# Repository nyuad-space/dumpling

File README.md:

## Hardware Errata v1 (2025)

- Pull down Boot1 instead of floating. For booting F405 with DFU, hold down the 3rd reset button.
- SWD TagConnect: Layout is too close to XT30 or M.2 sockets and connector is difficult to source.
- DRC check (recheck unconnected items).
- Look out for "x"ed POS in the BOM file. May have been accidentally toggled off.
- Reset button is too small & hard to reach
- Vertical USB is less stress-tolerant (pulls on solder)
- STM32F411 DFU bootloading error
- Check forward current rating for Schottky diodes.
- Consider using more current sensors i.e. Measure current draw from each board, from VIN total etc.
- Add in extra LEDs, buttons, etc. for extra functions/debugging in the future
- Unless saving space is a priority, consider using 0603 instead of 0402 for easier potential fixes
- Misc. Consider a more impact-tolerant casing to protect board upon landing

# Data Dumpling

Data Dumpling is a modular, high-speed data logger for MEMS sensors, designed as a payload for our experimental sounding rocket Stage Fright (2025). It enables real-time characterization and benchmarking of commercial sensors in demanding flight environments. The project aims to support sensor research and promote scalable, plug-and-play architectures for future space missions.

---

## Features

- **Modular Architecture**: Hot-swappable M.2 sensor ports with dedicated coprocessors  
- **Sensor Compatibility**: Supports I2C/SPI sensors with auto-detection via WHO_AM_I or equivalent registers  
- **Dedicated Flash Memory**: Each sensor board logs to onboard 16MB non-volatile memory  
- **Universal Firmware**: One firmware for all sensor types—detects, initializes, logs, and stores automatically  
- **Flight-Triggered Logging**: Dual-buffered flash logging triggered by flight detection events  
- **Core MCU**: STM32F405 manages flight readiness and triggers; STM32F411 handles individual sensor boards  
- **Post-Flight Retrieval**: Optionally offloads sensor data to SD card after recovery  

---

## Applications

- Benchmarking MEMS sensors in realistic aerospace environments  
- Development of sensor fusion algorithms and accurate sensor models  
- Modular data collection for experimental payloads  
- Plug-and-play architecture for custom flight computers and high-speed telemetry systems  

---

## Mainboard Components

| Type        | Components                                    |
|-------------|-----------------------------------------------|
| Main MCU    | STM32F405RGT                                  |
| Coprocessor | STM32F411CEU6                                 |
| IMUs        | LSM6DSO32, BMI088                              |
| Barometers  | DPS310XTSA1, BMP390L                           |
| Magnetometer| LIS2MDLTR                                      |
| Temperature | HDC3022DEJR                                    |
| Flash       | 16MB SPI NOR Flash per sensor board           |
| Recovery    | SD card slot for post-flight data offload     |

---

## Firmware Overview

Each STM32 microcontroller is programmed via built-in USB DFU bootloader.

### Main processor
- Communicates with MPU6050 to determine upright position
- Triggers flight monitoring upon launch detection
- Manages three flash files:
  - **Circular Buffer**: Logs during flight-ready state with overwrite on overflow  
  - **Main Buffer**: Logs during flight, no wrap-around  
  - **Status File**: Logs sensor configuration, buffer states, memory info, etc.  

### Coprocessor
Each sensor board follows this universal sequence:

1. Detect sensor using WHO_AM_I (or equivalent)  
2. Initialize I2C or SPI communication  
3. Configure sensor parameters (range, ODR, oversampling, filters)  
4. Initialize filesystem and create sensor-specific files  
5. Log sensor data at configured rate to flash memory  

---

## Future Improvements

- Integrate RTOS for multitasking, task prioritization, and modular firmware structure
- Add wireless/CAN telemetry  
- Increase flash capacity and add compression  
- Expand to include GNSS, radiation, and vibration sensors  
- Enable real-time in-flight filtering and basic analytics
- Use UART for master-slave communication in Arduino framework (SPI doesn't support it by default)
- Ensure unique flash IDs and file headers per sensor for proper data parsing

---

## Notes

- Designed for SRAD rocketry — ensure proper mechanical and EMI shielding  
- Verify sensor electrical compatibility before connecting new boards  
- Maintain synchronized firmware versions across all sensor modules  
- Follow proper ESD precautions during handling and flashing  

---

## Disclaimer

Use the files, hardware, and software in this repository at your own risk.  
We assume no liability for hardware damage, software malfunction, or unexpected behavior, particularly during live flight testing.  
Always validate your configuration through extensive ground testing.

---

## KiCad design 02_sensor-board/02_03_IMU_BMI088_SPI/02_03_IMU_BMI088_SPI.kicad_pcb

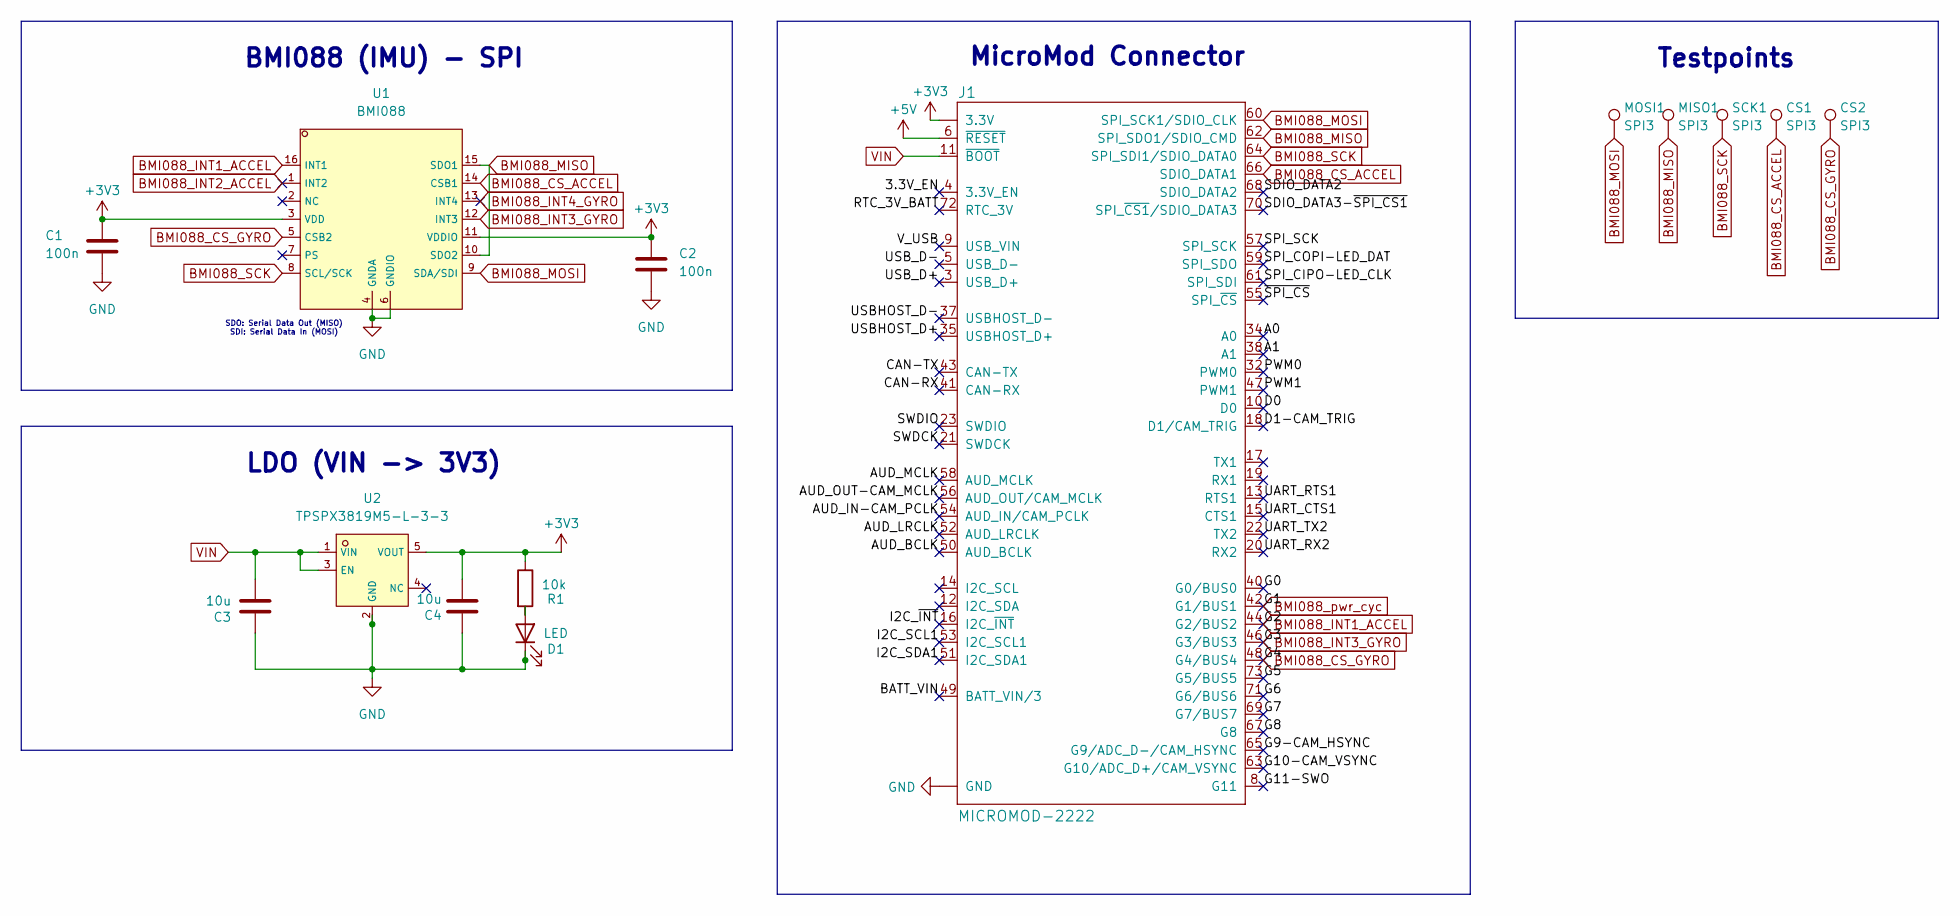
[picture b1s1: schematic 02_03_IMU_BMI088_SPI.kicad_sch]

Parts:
C1, C2: 100n; C_0402_1005Metric
C3, C4: 10u; C_1206_3216Metric
CS1, CS2: SPI3; TestPoint_Pad_D1.0mm
D1: LED; LED_0603_1608Metric
J1: MICROMOD-2222; M.2-CARD-E-22
MISO1: SPI3; TestPoint_Pad_D1.0mm
MOSI1: SPI3; TestPoint_Pad_D1.0mm
R1: 10k; R_0603_1608Metric
SCK1: SPI3; TestPoint_Pad_D1.0mm
U1: BMI088; LGA-16_L4.5-W3.0-P0.50-BL; LCSC C194919
U2: TPSPX3819M5-L-3-3; SOT-23-5_L3.0-W1.6-P0.95-LS2.8-BR; LCSC C5370980

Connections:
+3V3: C1.1, C2.1, C4.1, J1.2 (3.3V), J1.74 (3.3V), R1.1, U1.3 (VDD), U1.11 (VDDIO), U2.5 (VOUT)
+5V: J1.6 (~RESET)
/3.3V_EN: J1.4 (3.3V_EN)
/A0: J1.34 (A0)
/A1: J1.38 (A1)
/AUD_BCLK: J1.50 (AUD_BCLK)
/AUD_IN-CAM_PCLK: J1.54 (AUD_IN/CAM_PCLK)
/AUD_LRCLK: J1.52 (AUD_LRCLK)
/AUD_MCLK: J1.58 (AUD_MCLK)
/AUD_OUT-CAM_MCLK: J1.56 (AUD_OUT/CAM_MCLK)
/BATT_VIN: J1.49 (BATT_VIN/3)
/CAN-RX: J1.41 (CAN-RX)
/CAN-TX: J1.43 (CAN-TX)
/D0: J1.10 (D0)
/D1-CAM_TRIG: J1.18 (D1/CAM_TRIG)
/G0: J1.40 (G0/BUS0)
/G5: J1.73 (G5/BUS5)
/G6: J1.71 (G6/BUS6)
/G7: J1.69 (G7/BUS7)
/G8: J1.67 (G8)
/G9-CAM_HSYNC: J1.65 (G9/ADC_D-/CAM_HSYNC)
/G10-CAM_VSYNC: J1.63 (G10/ADC_D+/CAM_VSYNC)
/G11-SWO: J1.8 (G11)
/I2C_SCL1: J1.53 (I2C_SCL1)
/I2C_SDA1: J1.51 (I2C_SDA1)
/I2C_~INT: J1.16 (I2C_~INT)
/PWM0: J1.32 (PWM0)
/PWM1: J1.47 (PWM1)
/RTC_3V_BATT: J1.72 (RTC_3V)
/SDIO_DATA2: J1.68 (SDIO_DATA2)
/SDIO_DATA3-~SPI_CS1: J1.70 (SPI_~CS1/SDIO_DATA3)
/SPI_CIPO-LED_CLK: J1.61 (SPI_SDI)
/SPI_COPI-LED_DAT: J1.59 (SPI_SDO)
/SPI_SCK: J1.57 (SPI_SCK)
/SWDCK: J1.21 (SWDCK)
/SWDIO: J1.23 (SWDIO)
/UART_CTS1: J1.15 (CTS1)
/UART_RTS1: J1.13 (RTS1)
/UART_RX2: J1.20 (RX2)
/UART_TX2: J1.22 (TX2)
/USBHOST_D+: J1.35 (USBHOST_D+)
/USBHOST_D-: J1.37 (USBHOST_D-)
/USB_D+: J1.3 (USB_D+)
/USB_D-: J1.5 (USB_D-)
/V_USB: J1.9 (USB_VIN)
/~SPI_CS: J1.55 (SPI_~CS)
BMI088_CS_ACCEL: CS1.1, J1.66 (SDIO_DATA1), U1.14 (CSB1)
BMI088_CS_GYRO: CS2.1, J1.48 (G4/BUS4), U1.5 (CSB2)
BMI088_INT1_ACCEL: J1.44 (G2/BUS2), U1.16 (INT1)
BMI088_INT2_ACCEL: U1.1 (INT2)
BMI088_INT3_GYRO: J1.46 (G3/BUS3), U1.12 (INT3)
BMI088_INT4_GYRO: U1.13 (INT4)
BMI088_MISO: J1.62 (SPI_SDO1/SDIO_CMD), MISO1.1, U1.10 (SDO2), U1.15 (SDO1)
BMI088_MOSI: J1.60 (SPI_SCK1/SDIO_CLK), MOSI1.1, U1.9 (SDA/SDI)
BMI088_SCK: J1.64 (SPI_SDI1/SDIO_DATA0), SCK1.1, U1.8 (SCL/SCK)
BMI088_pwr_cyc: J1.42 (G1/BUS1)
GND: C1.2, C2.2, C3.2, C4.2, D1.1 (K), J1.1 (GND), J1.7 (GND), J1.33 (GND), J1.36 (GND), J1.39 (GND), J1.45 (GND), J1.75 (GND), J1.GND1 (GND), J1.GND2 (GND), J1.GND3 (GND), U1.4 (GNDA), U1.6 (GNDIO), U2.2 (GND)
unnamed: D1.2 (A), R1.2
VIN: C3.1, J1.11 (~BOOT), U2.1 (VIN), U2.3 (EN)

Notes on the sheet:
Testpoints
BMI088 (IMU) - SPI
SDO: Serial Data Out (MISO) SDI: Serial Data In (MOSI)
MicroMod Connector
LDO (VIN -> 3V3)

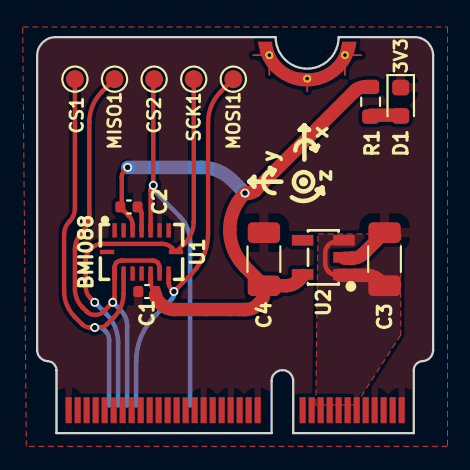
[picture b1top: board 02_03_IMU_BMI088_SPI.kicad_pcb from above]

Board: 2 copper layers, 22.0 x 22.0 mm, 16 parts (0 on the bottom side), 11 nets.

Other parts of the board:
FRAME1: FRAME-LEDGER; CREATIVE_COMMONS
LOGO1: SPECIAL_INSTRUCTIONS-ORDERING; ORDERING_INSTRUCTIONS

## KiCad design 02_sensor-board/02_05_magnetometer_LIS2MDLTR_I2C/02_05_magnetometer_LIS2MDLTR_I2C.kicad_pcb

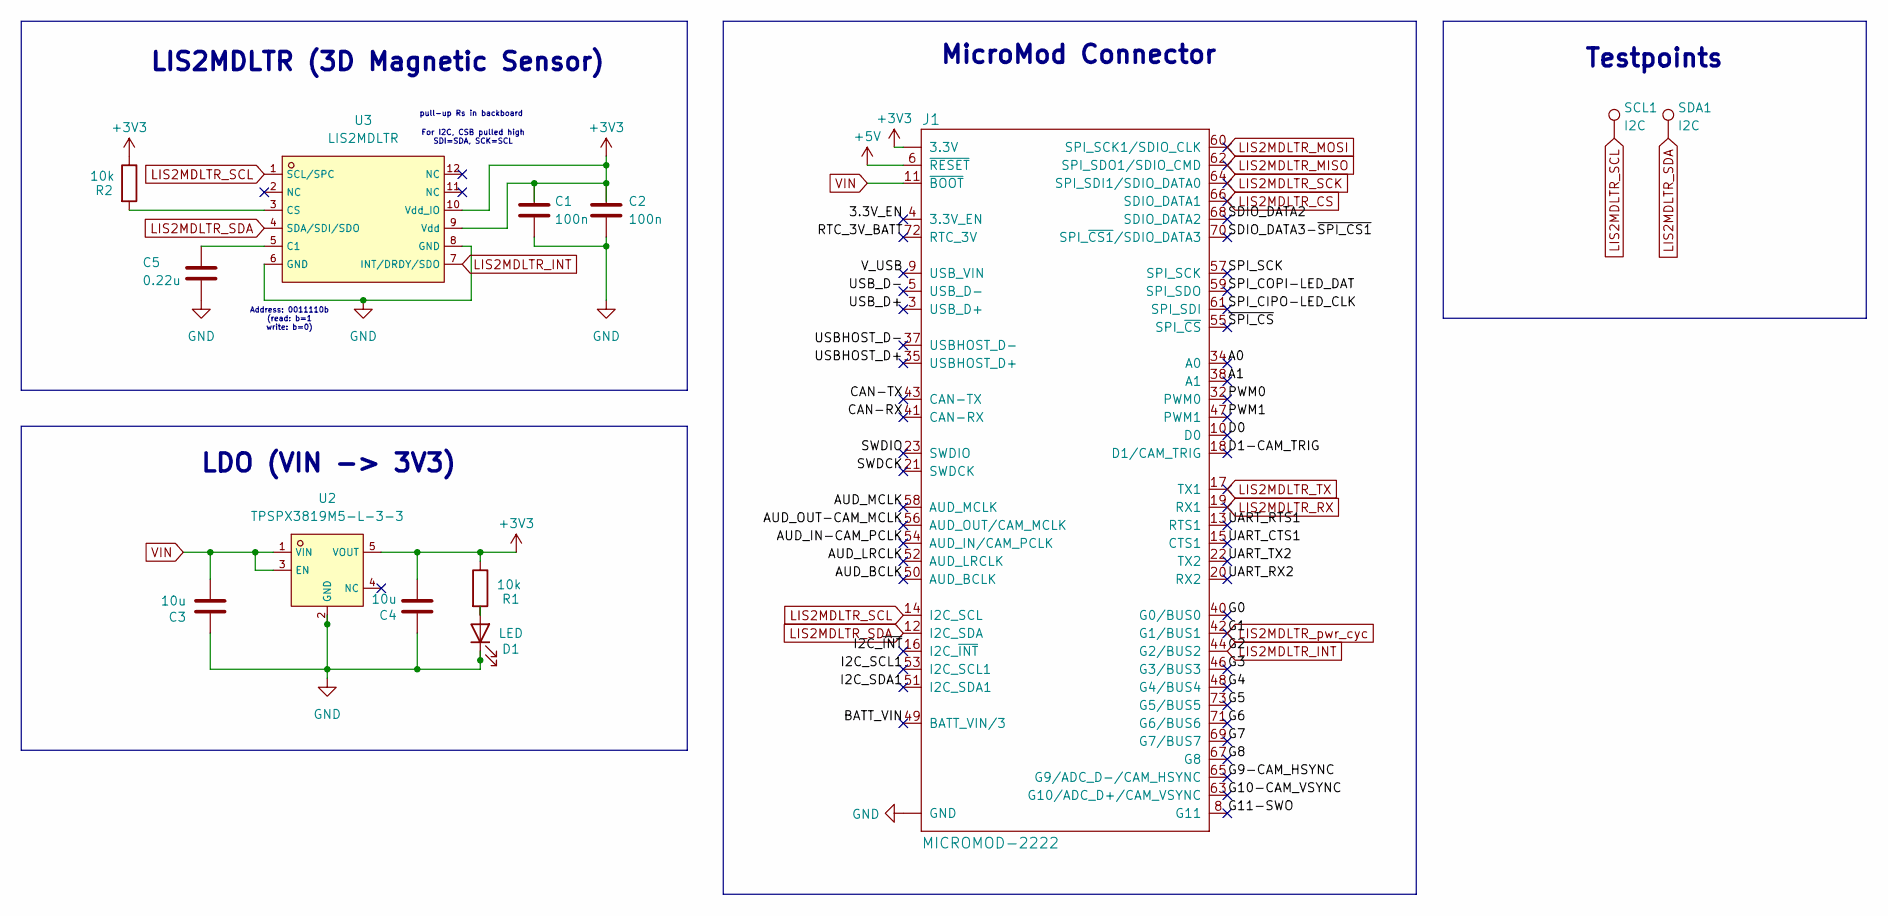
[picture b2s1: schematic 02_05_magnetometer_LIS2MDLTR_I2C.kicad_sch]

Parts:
C1, C2: 100n; C_0402_1005Metric
C3, C4: 10u; C_1206_3216Metric
C5: 0.22u; C_0402_1005Metric
D1: LED; LED_0603_1608Metric
J1: MICROMOD-2222; M.2-CARD-E-22
R1: 10k; R_0603_1608Metric
R2: 10k; R_0402_1005Metric
SCL1: I2C; TestPoint_Pad_D1.0mm
SDA1: I2C; TestPoint_Pad_D1.0mm
U2: TPSPX3819M5-L-3-3; SOT-23-5_L3.0-W1.6-P0.95-LS2.8-BR; LCSC C5370980
U3: LIS2MDLTR; LGA-12_L2.0-W2.0-P0.50-BL; LCSC C919695

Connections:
+3V3: C1.1, C2.1, C4.1, J1.2 (3.3V), J1.74 (3.3V), R1.1, R2.1, U2.5 (VOUT), U3.9 (Vdd), U3.10 (Vdd_IO)
+5V: J1.6 (~RESET)
/3.3V_EN: J1.4 (3.3V_EN)
/A0: J1.34 (A0)
/A1: J1.38 (A1)
/AUD_BCLK: J1.50 (AUD_BCLK)
/AUD_IN-CAM_PCLK: J1.54 (AUD_IN/CAM_PCLK)
/AUD_LRCLK: J1.52 (AUD_LRCLK)
/AUD_MCLK: J1.58 (AUD_MCLK)
/AUD_OUT-CAM_MCLK: J1.56 (AUD_OUT/CAM_MCLK)
/BATT_VIN: J1.49 (BATT_VIN/3)
/CAN-RX: J1.41 (CAN-RX)
/CAN-TX: J1.43 (CAN-TX)
/D0: J1.10 (D0)
/D1-CAM_TRIG: J1.18 (D1/CAM_TRIG)
/G0: J1.40 (G0/BUS0)
/G3: J1.46 (G3/BUS3)
/G4: J1.48 (G4/BUS4)
/G5: J1.73 (G5/BUS5)
/G6: J1.71 (G6/BUS6)
/G7: J1.69 (G7/BUS7)
/G8: J1.67 (G8)
/G9-CAM_HSYNC: J1.65 (G9/ADC_D-/CAM_HSYNC)
/G10-CAM_VSYNC: J1.63 (G10/ADC_D+/CAM_VSYNC)
/G11-SWO: J1.8 (G11)
/I2C_SCL1: J1.53 (I2C_SCL1)
/I2C_SDA1: J1.51 (I2C_SDA1)
/I2C_~INT: J1.16 (I2C_~INT)
/PWM0: J1.32 (PWM0)
/PWM1: J1.47 (PWM1)
/RTC_3V_BATT: J1.72 (RTC_3V)
/SDIO_DATA2: J1.68 (SDIO_DATA2)
/SDIO_DATA3-~SPI_CS1: J1.70 (SPI_~CS1/SDIO_DATA3)
/SPI_CIPO-LED_CLK: J1.61 (SPI_SDI)
/SPI_COPI-LED_DAT: J1.59 (SPI_SDO)
/SPI_SCK: J1.57 (SPI_SCK)
/SWDCK: J1.21 (SWDCK)
/SWDIO: J1.23 (SWDIO)
/UART_CTS1: J1.15 (CTS1)
/UART_RTS1: J1.13 (RTS1)
/UART_RX2: J1.20 (RX2)
/UART_TX2: J1.22 (TX2)
/USBHOST_D+: J1.35 (USBHOST_D+)
/USBHOST_D-: J1.37 (USBHOST_D-)
/USB_D+: J1.3 (USB_D+)
/USB_D-: J1.5 (USB_D-)
/V_USB: J1.9 (USB_VIN)
/~SPI_CS: J1.55 (SPI_~CS)
GND: C1.2, C2.2, C3.2, C4.2, C5.2, D1.1 (K), J1.1 (GND), J1.7 (GND), J1.33 (GND), J1.36 (GND), J1.39 (GND), J1.45 (GND), J1.75 (GND), J1.GND1 (GND), J1.GND2 (GND), J1.GND3 (GND), U2.2 (GND), U3.6 (GND), U3.8 (GND)
LIS2MDLTR_CS: J1.66 (SDIO_DATA1)
LIS2MDLTR_INT: J1.44 (G2/BUS2), U3.7 (INT/DRDY/SDO)
LIS2MDLTR_MISO: J1.62 (SPI_SDO1/SDIO_CMD)
LIS2MDLTR_MOSI: J1.60 (SPI_SCK1/SDIO_CLK)
LIS2MDLTR_RX: J1.19 (RX1)
LIS2MDLTR_SCK: J1.64 (SPI_SDI1/SDIO_DATA0)
LIS2MDLTR_SCL: J1.14 (I2C_SCL), SCL1.1, U3.1 (SCL/SPC)
LIS2MDLTR_SDA: J1.12 (I2C_SDA), SDA1.1, U3.4 (SDA/SDI/SDO)
LIS2MDLTR_TX: J1.17 (TX1)
LIS2MDLTR_pwr_cyc: J1.42 (G1/BUS1)
unnamed: D1.2 (A), R1.2
unnamed: C5.1, U3.5 (C1)
unnamed: R2.2, U3.3 (CS)
VIN: C3.1, J1.11 (~BOOT), U2.1 (VIN), U2.3 (EN)

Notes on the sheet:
pull-up Rs in backboard
Address: 0011110b (read: b=1 write: b=0)
MicroMod Connector
LDO (VIN -> 3V3)
LIS2MDLTR (3D Magnetic Sensor)
For I2C, CSB pulled high SDI=SDA, SCK=SCL
Testpoints

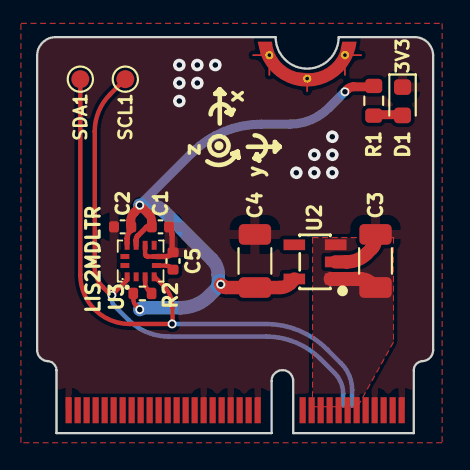
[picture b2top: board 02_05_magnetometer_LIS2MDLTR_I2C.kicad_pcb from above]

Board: 2 copper layers, 22.0 x 22.0 mm, 15 parts (0 on the bottom side), 9 nets.

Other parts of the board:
FRAME1: FRAME-LEDGER; CREATIVE_COMMONS
LOGO1: SPECIAL_INSTRUCTIONS-ORDERING; ORDERING_INSTRUCTIONS

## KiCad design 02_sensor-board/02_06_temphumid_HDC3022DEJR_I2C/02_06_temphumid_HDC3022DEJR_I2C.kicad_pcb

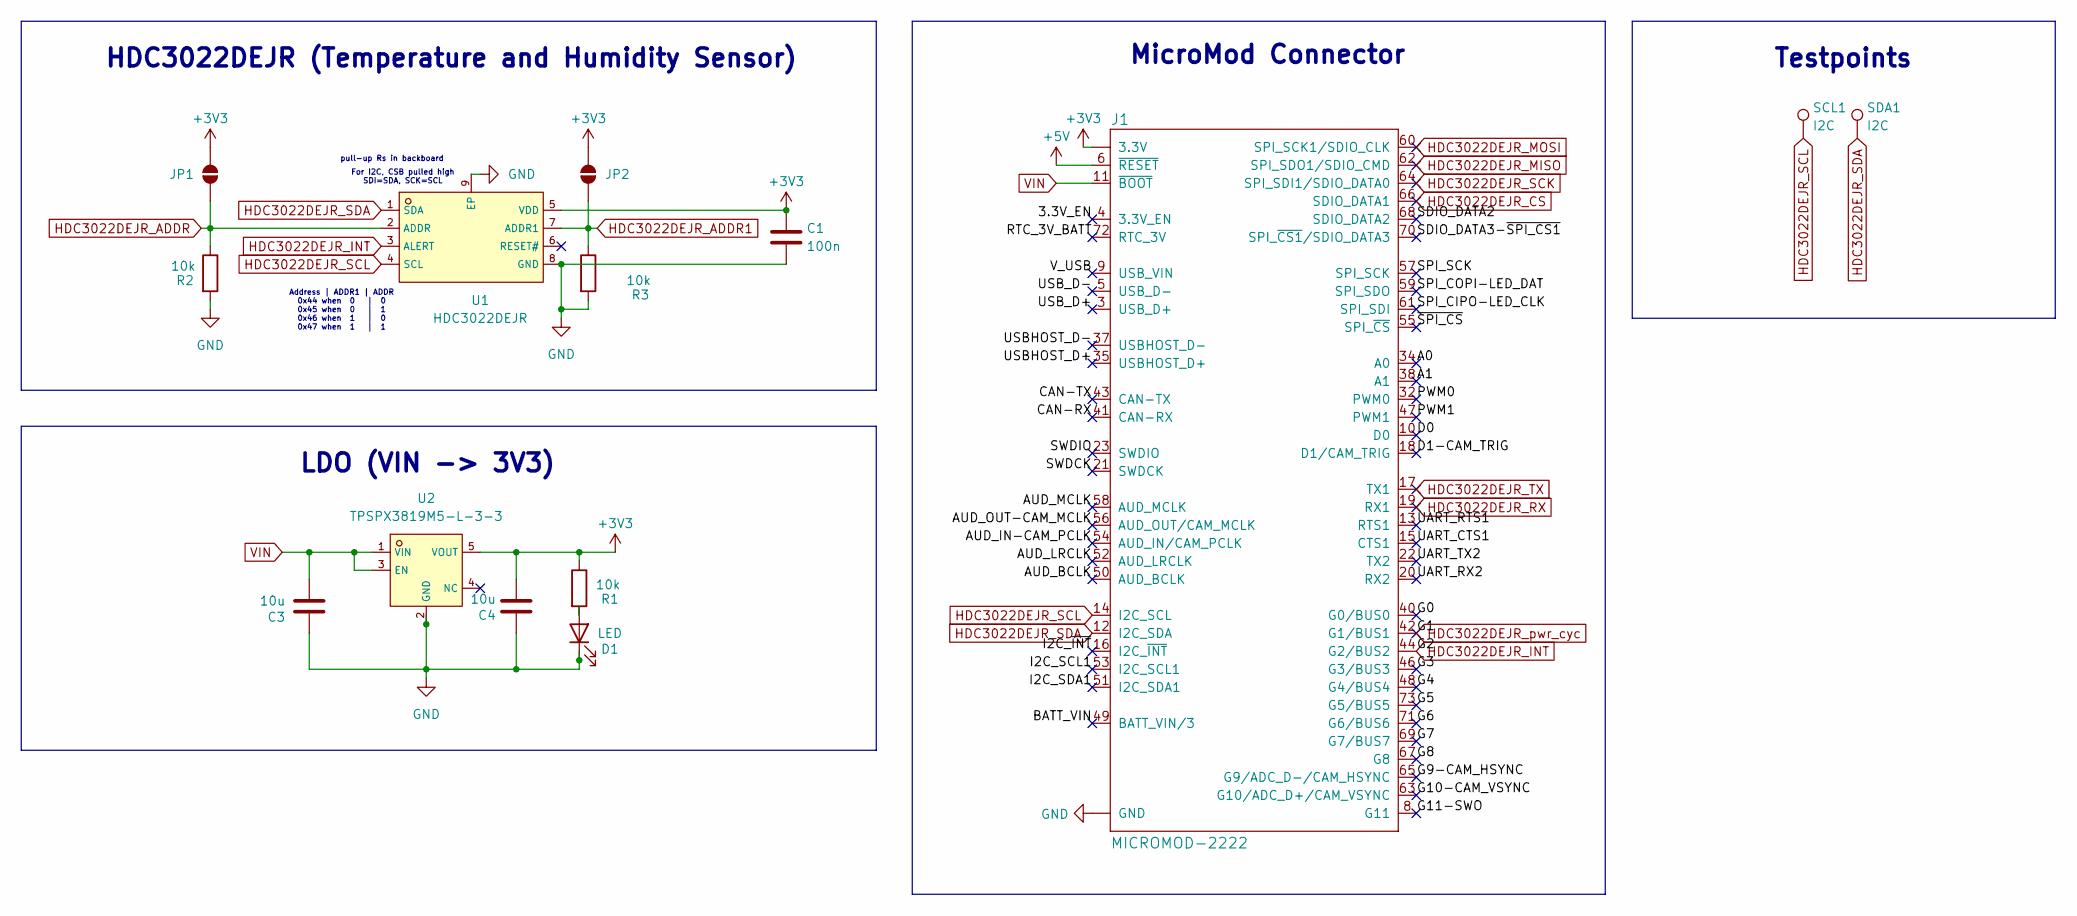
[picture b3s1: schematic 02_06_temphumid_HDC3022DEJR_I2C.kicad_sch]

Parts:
C1: 100n; C_0402_1005Metric
C3, C4: 10u; C_1206_3216Metric
D1: LED; LED_0603_1608Metric
J1: MICROMOD-2222; M.2-CARD-E-22
JP1, JP2: SolderJumper_2_Open; SolderJumper-2_P1.3mm_Open_Pad1.0x1.5mm
R1: 10k; R_0603_1608Metric
R2, R3: 10k; R_0402_1005Metric
SCL1: I2C; TestPoint_Pad_D1.0mm
SDA1: I2C; TestPoint_Pad_D1.0mm
U1: HDC3022DEJR; TDFN-8_L2.5-W2.5-P0.50-BL-EP; LCSC C17434731
U2: TPSPX3819M5-L-3-3; SOT-23-5_L3.0-W1.6-P0.95-LS2.8-BR; LCSC C5370980

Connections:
+3V3: C1.1, C4.1, J1.2 (3.3V), J1.74 (3.3V), JP1.2 (B), JP2.2 (B), R1.1, U1.5 (VDD), U2.5 (VOUT)
+5V: J1.6 (~RESET)
/3.3V_EN: J1.4 (3.3V_EN)
/A0: J1.34 (A0)
/A1: J1.38 (A1)
/AUD_BCLK: J1.50 (AUD_BCLK)
/AUD_IN-CAM_PCLK: J1.54 (AUD_IN/CAM_PCLK)
/AUD_LRCLK: J1.52 (AUD_LRCLK)
/AUD_MCLK: J1.58 (AUD_MCLK)
/AUD_OUT-CAM_MCLK: J1.56 (AUD_OUT/CAM_MCLK)
/BATT_VIN: J1.49 (BATT_VIN/3)
/CAN-RX: J1.41 (CAN-RX)
/CAN-TX: J1.43 (CAN-TX)
/D0: J1.10 (D0)
/D1-CAM_TRIG: J1.18 (D1/CAM_TRIG)
/G0: J1.40 (G0/BUS0)
/G3: J1.46 (G3/BUS3)
/G4: J1.48 (G4/BUS4)
/G5: J1.73 (G5/BUS5)
/G6: J1.71 (G6/BUS6)
/G7: J1.69 (G7/BUS7)
/G8: J1.67 (G8)
/G9-CAM_HSYNC: J1.65 (G9/ADC_D-/CAM_HSYNC)
/G10-CAM_VSYNC: J1.63 (G10/ADC_D+/CAM_VSYNC)
/G11-SWO: J1.8 (G11)
/I2C_SCL1: J1.53 (I2C_SCL1)
/I2C_SDA1: J1.51 (I2C_SDA1)
/I2C_~INT: J1.16 (I2C_~INT)
/PWM0: J1.32 (PWM0)
/PWM1: J1.47 (PWM1)
/RTC_3V_BATT: J1.72 (RTC_3V)
/SDIO_DATA2: J1.68 (SDIO_DATA2)
/SDIO_DATA3-~SPI_CS1: J1.70 (SPI_~CS1/SDIO_DATA3)
/SPI_CIPO-LED_CLK: J1.61 (SPI_SDI)
/SPI_COPI-LED_DAT: J1.59 (SPI_SDO)
/SPI_SCK: J1.57 (SPI_SCK)
/SWDCK: J1.21 (SWDCK)
/SWDIO: J1.23 (SWDIO)
/UART_CTS1: J1.15 (CTS1)
/UART_RTS1: J1.13 (RTS1)
/UART_RX2: J1.20 (RX2)
/UART_TX2: J1.22 (TX2)
/USBHOST_D+: J1.35 (USBHOST_D+)
/USBHOST_D-: J1.37 (USBHOST_D-)
/USB_D+: J1.3 (USB_D+)
/USB_D-: J1.5 (USB_D-)
/V_USB: J1.9 (USB_VIN)
/~SPI_CS: J1.55 (SPI_~CS)
GND: C1.2, C3.2, C4.2, D1.1 (K), J1.1 (GND), J1.7 (GND), J1.33 (GND), J1.36 (GND), J1.39 (GND), J1.45 (GND), J1.75 (GND), J1.GND1 (GND), J1.GND2 (GND), J1.GND3 (GND), R2.2, R3.2, U1.8 (GND), U1.9 (EP), U2.2 (GND)
HDC3022DEJR_ADDR: JP1.1 (A), R2.1, U1.2 (ADDR)
HDC3022DEJR_ADDR1: JP2.1 (A), R3.1, U1.7 (ADDR1)
HDC3022DEJR_CS: J1.66 (SDIO_DATA1)
HDC3022DEJR_INT: J1.44 (G2/BUS2), U1.3 (ALERT)
HDC3022DEJR_MISO: J1.62 (SPI_SDO1/SDIO_CMD)
HDC3022DEJR_MOSI: J1.60 (SPI_SCK1/SDIO_CLK)
HDC3022DEJR_RX: J1.19 (RX1)
HDC3022DEJR_SCK: J1.64 (SPI_SDI1/SDIO_DATA0)
HDC3022DEJR_SCL: J1.14 (I2C_SCL), SCL1.1, U1.4 (SCL)
HDC3022DEJR_SDA: J1.12 (I2C_SDA), SDA1.1, U1.1 (SDA)
HDC3022DEJR_TX: J1.17 (TX1)
HDC3022DEJR_pwr_cyc: J1.42 (G1/BUS1)
unnamed: D1.2 (A), R1.2
VIN: C3.1, J1.11 (~BOOT), U2.1 (VIN), U2.3 (EN)

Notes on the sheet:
Address | ADDR1 | ADDR 0x44 when 0 | 0 0x45 when 0 | 1 0x46 when 1 | 0 0x47 when 1 | 1
pull-up Rs in backboard
LDO (VIN -> 3V3)
For I2C, CSB pulled high SDI=SDA, SCK=SCL
MicroMod Connector
HDC3022DEJR (Temperature and Humidity Sensor)
Testpoints

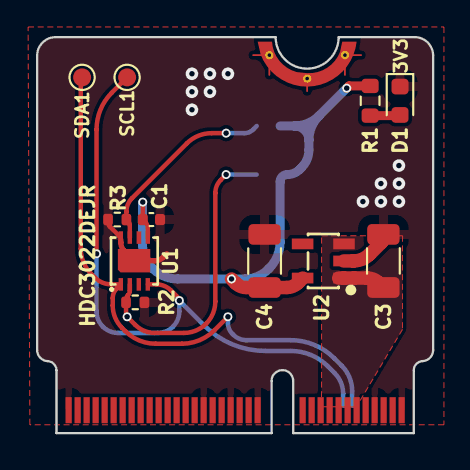
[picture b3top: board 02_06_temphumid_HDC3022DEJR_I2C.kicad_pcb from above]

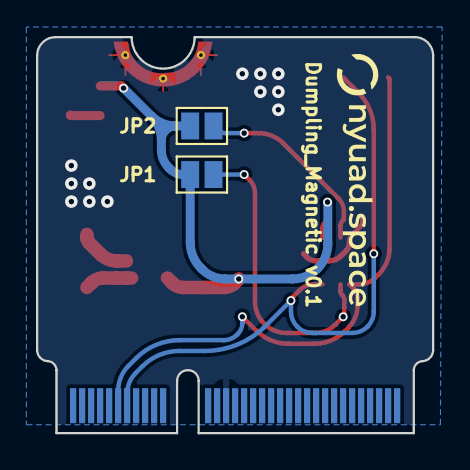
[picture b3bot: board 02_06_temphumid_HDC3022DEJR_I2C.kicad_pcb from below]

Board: 2 copper layers, 22.0 x 22.0 mm, 16 parts (2 on the bottom side), 9 nets.

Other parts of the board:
FRAME1: FRAME-LEDGER; CREATIVE_COMMONS
LOGO1: SPECIAL_INSTRUCTIONS-ORDERING; ORDERING_INSTRUCTIONS

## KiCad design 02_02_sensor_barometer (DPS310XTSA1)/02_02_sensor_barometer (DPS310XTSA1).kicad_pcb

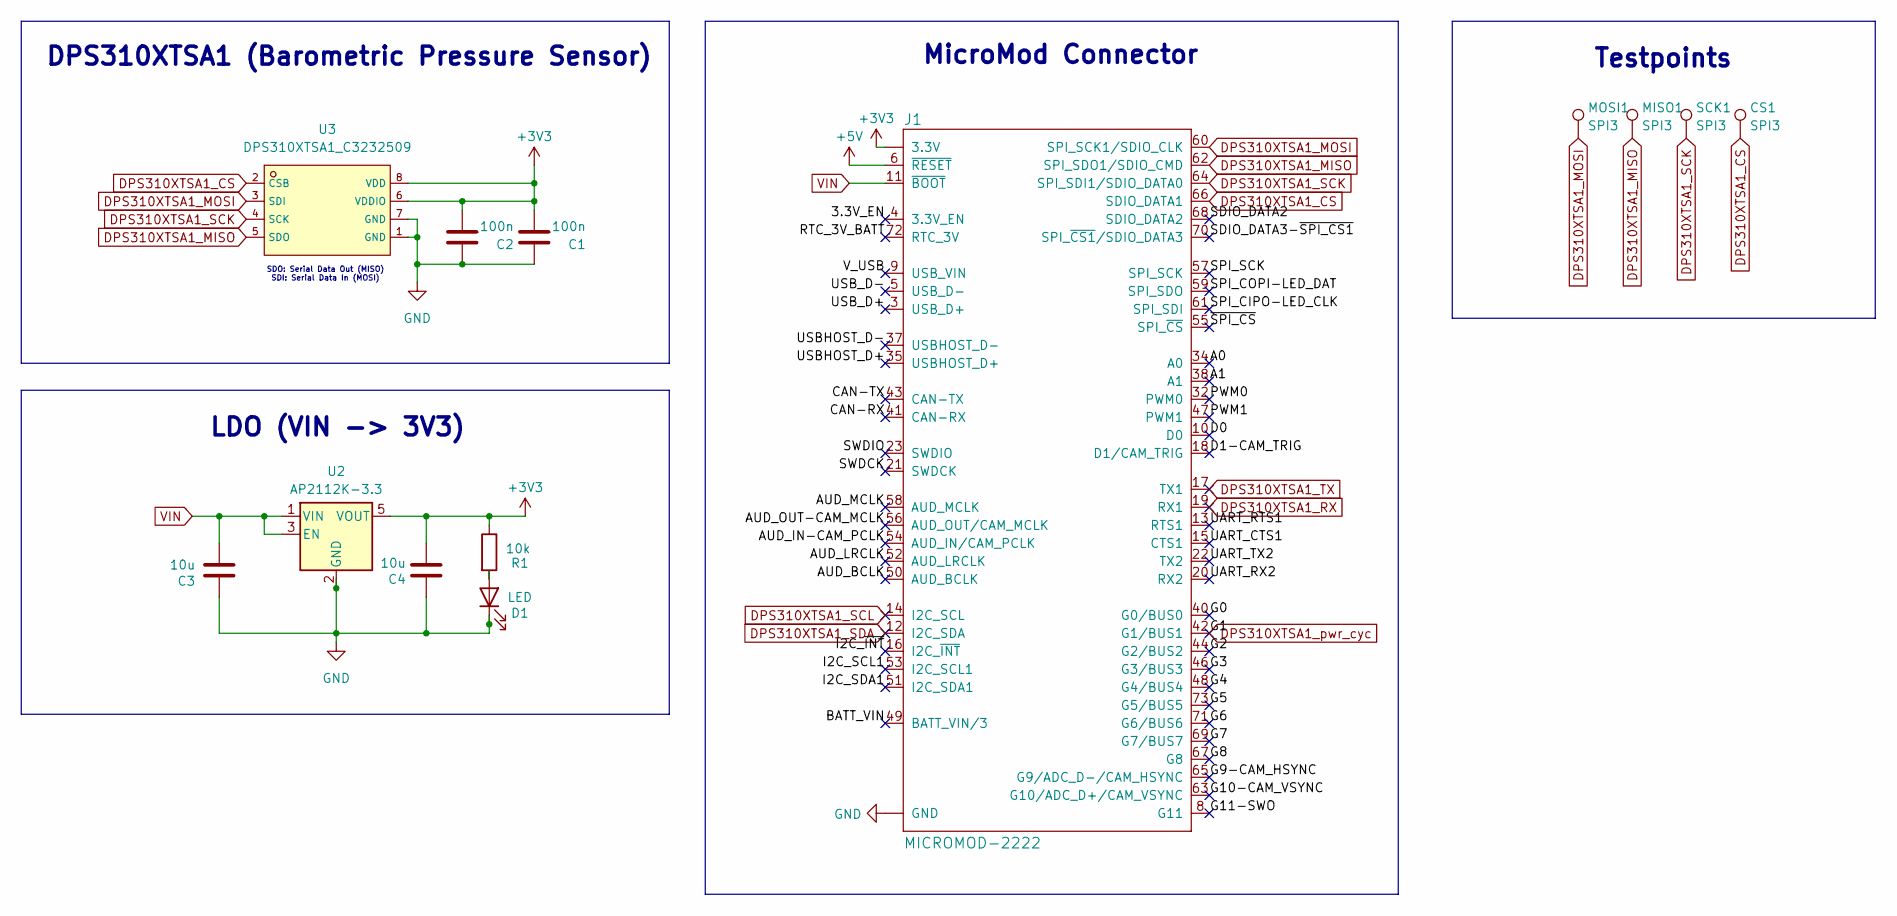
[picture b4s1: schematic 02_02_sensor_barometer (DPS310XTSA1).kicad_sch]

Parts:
C1, C2: 100n; C_0402_1005Metric
C3, C4: 10u; C_1206_3216Metric
CS1: SPI3; TestPoint_Pad_D1.0mm
D1: LED; LED_0603_1608Metric
J1: MICROMOD-2222; M.2-CARD-E-22
MISO1: SPI3; TestPoint_Pad_D1.0mm
MOSI1: SPI3; TestPoint_Pad_D1.0mm
R1: 10k; R_0603_1608Metric
SCK1: SPI3; TestPoint_Pad_D1.0mm
U2: AP2112K-3.3; SOT-23-5
U3: DPS310XTSA1_C3232509; LGA-8_DPS310XTSA1; LCSC C3232509

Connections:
+3V3: C1.1, C2.1, C4.1, J1.2 (3.3V), J1.74 (3.3V), R1.1, U2.5 (VOUT), U3.6 (VDDIO), U3.8 (VDD)
+5V: J1.6 (~RESET)
/3.3V_EN: J1.4 (3.3V_EN)
/A0: J1.34 (A0)
/A1: J1.38 (A1)
/AUD_BCLK: J1.50 (AUD_BCLK)
/AUD_IN-CAM_PCLK: J1.54 (AUD_IN/CAM_PCLK)
/AUD_LRCLK: J1.52 (AUD_LRCLK)
/AUD_MCLK: J1.58 (AUD_MCLK)
/AUD_OUT-CAM_MCLK: J1.56 (AUD_OUT/CAM_MCLK)
/BATT_VIN: J1.49 (BATT_VIN/3)
/CAN-RX: J1.41 (CAN-RX)
/CAN-TX: J1.43 (CAN-TX)
/D0: J1.10 (D0)
/D1-CAM_TRIG: J1.18 (D1/CAM_TRIG)
/G0: J1.40 (G0/BUS0)
/G2: J1.44 (G2/BUS2)
/G3: J1.46 (G3/BUS3)
/G4: J1.48 (G4/BUS4)
/G5: J1.73 (G5/BUS5)
/G6: J1.71 (G6/BUS6)
/G7: J1.69 (G7/BUS7)
/G8: J1.67 (G8)
/G9-CAM_HSYNC: J1.65 (G9/ADC_D-/CAM_HSYNC)
/G10-CAM_VSYNC: J1.63 (G10/ADC_D+/CAM_VSYNC)
/G11-SWO: J1.8 (G11)
/I2C_SCL1: J1.53 (I2C_SCL1)
/I2C_SDA1: J1.51 (I2C_SDA1)
/I2C_~INT: J1.16 (I2C_~INT)
/PWM0: J1.32 (PWM0)
/PWM1: J1.47 (PWM1)
/RTC_3V_BATT: J1.72 (RTC_3V)
/SDIO_DATA2: J1.68 (SDIO_DATA2)
/SDIO_DATA3-~SPI_CS1: J1.70 (SPI_~CS1/SDIO_DATA3)
/SPI_CIPO-LED_CLK: J1.61 (SPI_SDI)
/SPI_COPI-LED_DAT: J1.59 (SPI_SDO)
/SPI_SCK: J1.57 (SPI_SCK)
/SWDCK: J1.21 (SWDCK)
/SWDIO: J1.23 (SWDIO)
/UART_CTS1: J1.15 (CTS1)
/UART_RTS1: J1.13 (RTS1)
/UART_RX2: J1.20 (RX2)
/UART_TX2: J1.22 (TX2)
/USBHOST_D+: J1.35 (USBHOST_D+)
/USBHOST_D-: J1.37 (USBHOST_D-)
/USB_D+: J1.3 (USB_D+)
/USB_D-: J1.5 (USB_D-)
/V_USB: J1.9 (USB_VIN)
/~SPI_CS: J1.55 (SPI_~CS)
DPS310XTSA1_CS: CS1.1, J1.66 (SDIO_DATA1), U3.2 (CSB)
DPS310XTSA1_MISO: J1.62 (SPI_SDO1/SDIO_CMD), MISO1.1, U3.5 (SDO); also elsewhere on the board
DPS310XTSA1_MOSI: J1.60 (SPI_SCK1/SDIO_CLK), MOSI1.1, U3.3 (SDI)
DPS310XTSA1_RX: J1.19 (RX1)
DPS310XTSA1_SCK: J1.64 (SPI_SDI1/SDIO_DATA0), SCK1.1, U3.4 (SCK)
DPS310XTSA1_SCL: J1.14 (I2C_SCL)
DPS310XTSA1_SDA: J1.12 (I2C_SDA)
DPS310XTSA1_TX: J1.17 (TX1)
DPS310XTSA1_pwr_cyc: J1.42 (G1/BUS1)
GND: C1.2, C2.2, C3.2, C4.2, D1.1 (K), J1.1 (GND), J1.7 (GND), J1.33 (GND), J1.36 (GND), J1.39 (GND), J1.45 (GND), J1.75 (GND), J1.GND1 (GND), J1.GND2 (GND), J1.GND3 (GND), U2.2 (GND), U3.1 (GND), U3.7 (GND)
unnamed: D1.2 (A), R1.2
VIN: C3.1, J1.11 (~BOOT), U2.1 (VIN), U2.3 (EN)

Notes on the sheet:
SDO: Serial Data Out (MISO) SDI: Serial Data In (MOSI)
DPS310XTSA1 (Barometric Pressure Sensor)
MicroMod Connector
Testpoints
LDO (VIN -> 3V3)

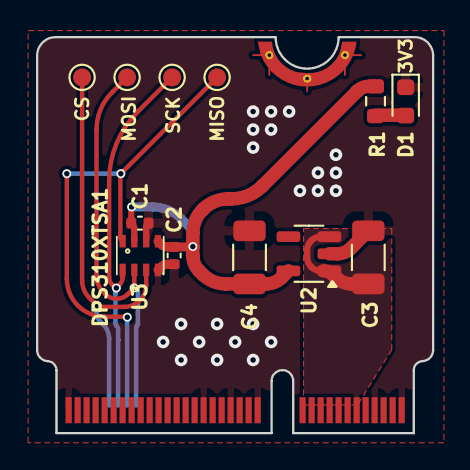
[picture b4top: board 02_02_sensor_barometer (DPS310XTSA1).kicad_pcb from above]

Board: 2 copper layers, 22.0 x 22.0 mm, 15 parts (0 on the bottom side), 8 nets.

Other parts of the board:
FRAME1: FRAME-LEDGER; CREATIVE_COMMONS
LOGO1: SPECIAL_INSTRUCTIONS-ORDERING; ORDERING_INSTRUCTIONS
MISO: SPI3; TestPoint_Pad_D1.0mm

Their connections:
DPS310XTSA1_MISO: MISO.1; also elsewhere on the board

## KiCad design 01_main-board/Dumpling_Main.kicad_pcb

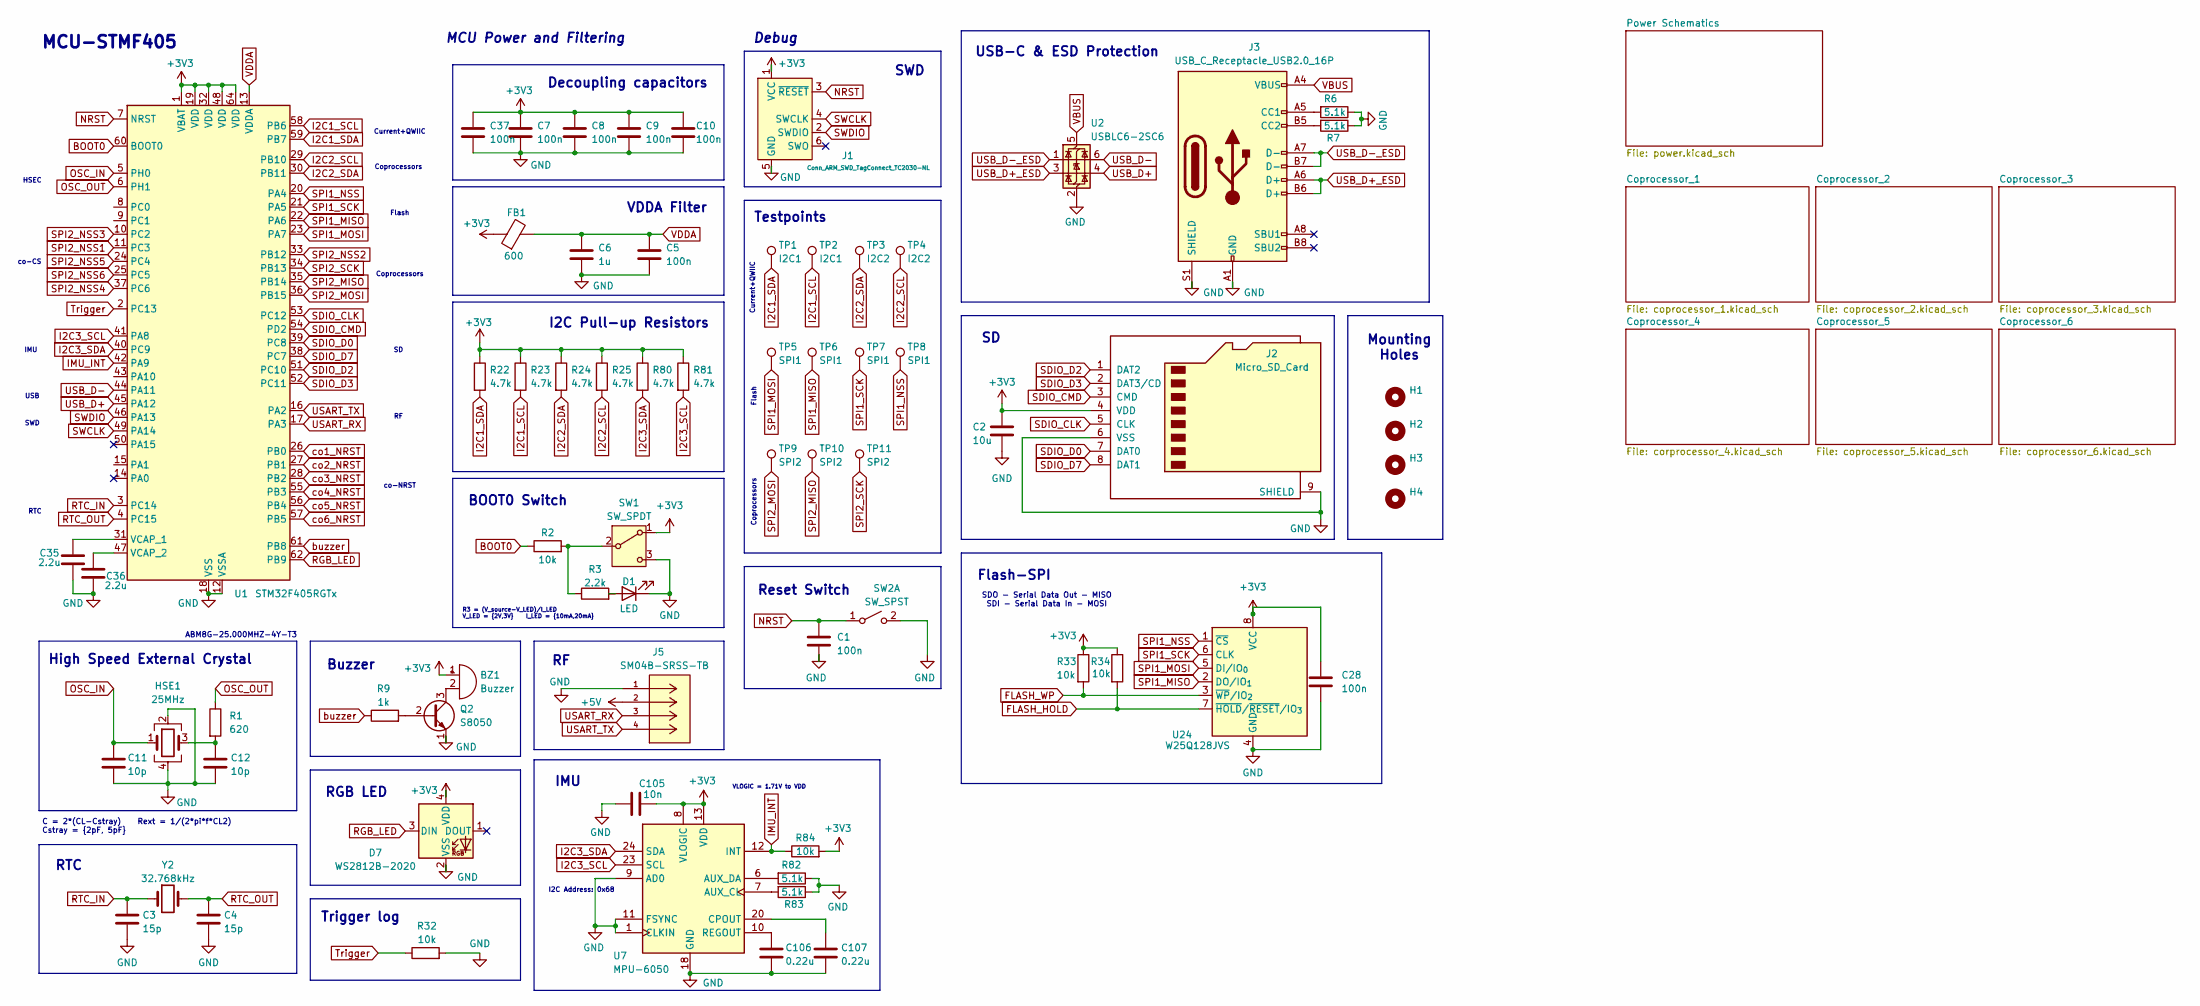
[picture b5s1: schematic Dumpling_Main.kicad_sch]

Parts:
BZ1: Buzzer; BUZ-SMD_FST-5030
C1, C5, C7, C8, C9, C10, C28, C37: 100n; C_0402_1005Metric
C2: 10u; C_0805_2012Metric
C3, C4: 15p; C_0402_1005Metric
C6: 1u; C_0402_1005Metric
C11, C12: 10p; C_0402_1005Metric
C35, C36: 2.2u; C_0603_1608Metric
C105: 10n; C_0402_1005Metric
C106, C107: 0.22u; C_0402_1005Metric
D1: LED; LED_0603_1608Metric
D7: WS2812B-2020; LED_WS2812B-2020_PLCC4_2.0x2.0mm
FB1: 600; L_0603_1608Metric
H1, H2, H3, H4: MountingHole; MountingHole_3.2mm_M3_Pad_Via
HSE1: 25MHz; Crystal_SMD_Abracon_ABM8G-4Pin_3.2x2.5mm
J1: Conn_ARM_SWD_TagConnect_TC2030-NL; Tag-Connect_TC2030-IDC-NL_2x03_P1.27mm_Vertical
J2: Micro_SD_Card; microSD_HC_Molex_47219-2001
J3: USB_C_Receptacle_USB2.0_16P; USB_C_Receptacle_G-Switch_GT-USB-7010ASV
J5: SM04B-SRSS-TB; JST_SH_SM04B-SRSS-TB_1x04-1MP_P1.00mm_Horizontal; MANUFACTURER_PART_NUMBER SM04B-SRSS-TB
Q2: S8050; SOT-23
R1: 620; C_0402_1005Metric
R2, R32, R33, R34, R84: 10k; R_0402_1005Metric
R3: 2.2k; R_0603_1608Metric
R6, R7, R82, R83: 5.1k; R_0402_1005Metric
R9: 1k; R_0402_1005Metric
R22, R23, R24, R25, R80, R81: 4.7k; R_0402_1005Metric
SW1: SW_SPDT; SW_JS102011JCQN
SW2: SW_SPST; SW_SPST_B3U-1000P
TP1, TP2: I2C1; TestPoint_Pad_D1.0mm
TP3, TP4: I2C2; TestPoint_Pad_D1.0mm
TP5, TP6, TP7, TP8: SPI1; TestPoint_Pad_D1.0mm
TP9, TP10, TP11: SPI2; TestPoint_Pad_D1.0mm
U1: STM32F405RGTx; LQFP-64_10x10mm_P0.5mm
U2: USBLC6-2SC6; SOT-23-6
U7: MPU-6050; InvenSense_QFN-24_4x4mm_P0.5mm
U24: W25Q128JVS; SOIC-8_5.3x5.3mm_P1.27mm
Y2: 32.768kHz; Crystal_SMD_3215-2Pin_3.2x1.5mm

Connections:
+5V: J5.2; also elsewhere on the board
BOOT0: R2.1, U1.60 (BOOT0)
FLASH_HOLD: R34.2, U24.7 (~HOLD/~RESET/IO_{3})
FLASH_WP: R33.2, U24.3 (~WP/IO_{2})
I2C1_SCL: R23.2, TP2.1, U1.58 (PB6); also elsewhere on the board
I2C1_SDA: R22.2, TP1.1, U1.59 (PB7); also elsewhere on the board
I2C2_SCL: R25.2, TP4.1, U1.29 (PB10); also elsewhere on the board
I2C2_SDA: R24.2, TP3.1, U1.30 (PB11); also elsewhere on the board
I2C3_SCL: R81.2, U1.41 (PA8), U7.23 (SCL)
I2C3_SDA: R80.2, U1.40 (PC9), U7.24 (SDA)
IMU_INT: R84.1, U1.42 (PA9), U7.12 (INT)
NRST: C1.1, J1.3 (~RESET), SW2.1 (A), U1.7 (NRST)
unnamed: BZ1.2 (-), Q2.3 (C)
unnamed: C12.1, HSE1.3, R1.2
unnamed: D1.2 (A), R3.2
unnamed: J3.A5 (CC1), R6.2
unnamed: J3.B5 (CC2), R7.2
unnamed: Q2.2 (B), R9.2
unnamed: R2.2, R3.1, SW1.2 (B)
unnamed: C35.1, U1.31 (VCAP_1)
unnamed: C36.1, U1.47 (VCAP_2)
unnamed: C107.1, U7.20 (CPOUT)
unnamed: C106.1, U7.10 (REGOUT)
unnamed 58: U7.2 (A0); also elsewhere on the board
OSC_IN: C11.1, HSE1.1, U1.5 (PH0)
OSC_OUT: R1.1, U1.6 (PH1)
RGB_LED: D7.3 (DIN), U1.62 (PB9)
RTC_IN: C3.1, U1.3 (PC14), Y2.1
RTC_OUT: C4.1, U1.4 (PC15), Y2.2
SDIO_CLK: J2.5 (CLK), U1.53 (PC12)
SDIO_CMD: J2.3 (CMD), U1.54 (PD2)
SDIO_D0: J2.7 (DAT0), U1.39 (PC8)
SDIO_D2: J2.1 (DAT2), U1.51 (PC10)
SDIO_D3: J2.2 (DAT3/CD), U1.52 (PC11)
SDIO_D7: J2.8 (DAT1), U1.38 (PC7)
SPI1_MISO: TP6.1, U1.22 (PA6), U24.2 (DO/IO_{1})
SPI1_MOSI: TP5.1, U1.23 (PA7), U24.5 (DI/IO_{0})
SPI1_NSS: TP8.1, U1.20 (PA4), U24.1 (~CS)
SPI1_SCK: TP7.1, U1.21 (PA5), U24.6 (CLK)
SPI2_MISO: TP10.1, U1.35 (PB14); also elsewhere on the board
SPI2_MOSI: TP9.1, U1.36 (PB15); also elsewhere on the board
SPI2_NSS1: U1.11 (PC3); also elsewhere on the board
SPI2_NSS2: U1.33 (PB12); also elsewhere on the board
SPI2_NSS3: U1.10 (PC2); also elsewhere on the board
SPI2_NSS4: U1.37 (PC6); also elsewhere on the board
SPI2_NSS5: U1.24 (PC4); also elsewhere on the board
SPI2_NSS6: U1.25 (PC5); also elsewhere on the board
SPI2_SCK: TP11.1, U1.34 (PB13); also elsewhere on the board
SWCLK: J1.4 (SWCLK), U1.49 (PA14)
SWDIO: J1.2 (SWDIO), U1.46 (PA13)
Trigger: R32.1, U1.2 (PC13); also elsewhere on the board
USART_RX: J5.3, U1.17 (PA3)
USART_TX: J5.4, U1.16 (PA2)
USB_D+: U1.45 (PA12), U2.4 (I/O2)
USB_D+_ESD: J3.A6 (D+), J3.B6 (D+), U2.3 (I/O2)
USB_D-: U1.44 (PA11), U2.6 (I/O1)
USB_D-_ESD: J3.A7 (D-), J3.B7 (D-), U2.1 (I/O1)
VBUS: J3.A4 (VBUS), J3.A9 (VBUS), J3.B4 (VBUS), J3.B9 (VBUS), U2.5 (VBUS); also elsewhere on the board
VDDA: C5.1, C6.1, FB1.2, U1.13 (VDDA)
buzzer: R9.1, U1.61 (PB8)
co1_NRST: U1.26 (PB0); also elsewhere on the board
co2_NRST: U1.27 (PB1); also elsewhere on the board
co3_NRST: U1.28 (PB2); also elsewhere on the board
co4_NRST: U1.55 (PB3); also elsewhere on the board
co5_NRST: U1.56 (PB4); also elsewhere on the board
co6_NRST: U1.57 (PB5); also elsewhere on the board

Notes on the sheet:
MCU-STMF405
Debug
IMU
SWD
RTC
Buzzer
Decoupling capacitors
Trigger log
Flash
co-NRST
MCU Power and Filtering
Coprocessors
R3 = (V_source-V_LED)/I_LED V_LED = {2V,3V} I_LED = {10mA,20mA}
ABM8G-25.000MHZ-4Y-T3
USB
VLOGIC = 1.71V to VDD
SDO - Serial Data Out - MISO SDI - Serial Data In - MOSI
BOOT0 Switch
Flash-SPI
Testpoints
RTC
Mounting Holes
RGB LED
co-CS
SWD
High Speed External Crystal
Current+QWIIC
I2C Pull-up Resistors
C = 2*(CL-Cstray) Rext = 1/(2*pi*f*CL2) Cstray = {2pF, 5pF}
HSEC
Reset Switch
I2C Address: 0x68
USB-C & ESD Protection
VDDA Filter

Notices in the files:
parts and their libraries:
COPYRIGHT: Copyright (C) 2024 Ultra Librarian. All rights reserved.
https://creativecommons.org/licenses/by-sa/4.0
Released under the Creative Commons Attribution Share-Alike 4.0 License
